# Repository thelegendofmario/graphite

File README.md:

# Graphite: Custom Graphing calculator

## What is this?

This is a custom-made graphing calculator built off of the [Rasberry Pi Picos](https://www.raspberrypi.com/products/raspberry-pi-pico/).
There are a couple of reasons I chose this board: 
1. they're cheap, and easy to get a hold of.
2. if a new one (with the same form factor and compatible pinout) comes out, you can swap it out, giving you a more powerful cpu, more storage, etc.

## But _Why_ did you make this?

I made this because this is my first ever PCB and thing like this. _Also_, I really wanted to fix some things that I found wrong with the TI-84s and such.

## Bill of Materials:

PCB components: 
| Name | Buy Website | Price | Notes |
| --- | --- | --- | --- |
| 2.2" TFT LCD | https://www.adafruit.com/product/1480 | $24.95 | Just have to use a generic 10 pin thingy 🤷 |
| Rasberry Pi Pico | https://www.adafruit.com/product/4864 | $6.00 |  |
| Buttons | https://www.mouser.com/ProductDetail/Omron-Electronics/B3F-1000?qs=lK7M36XCk6JQHckSc1xIsg%3D%3D | $0.25 | (that's for one, gets cheaper the more you buy yay) |
| male headers | https://www.adafruit.com/product/392 | $4.95 |  |
| 10 pin female headers | https://www.sparkfun.com/header-10-pin-female-pth-0-1.html | $0.80 |  |
| 20 pin female headers | https://www.adafruit.com/product/4155 | $2.50 |  |
|  | Total | $39.45 |  |

---

> project images

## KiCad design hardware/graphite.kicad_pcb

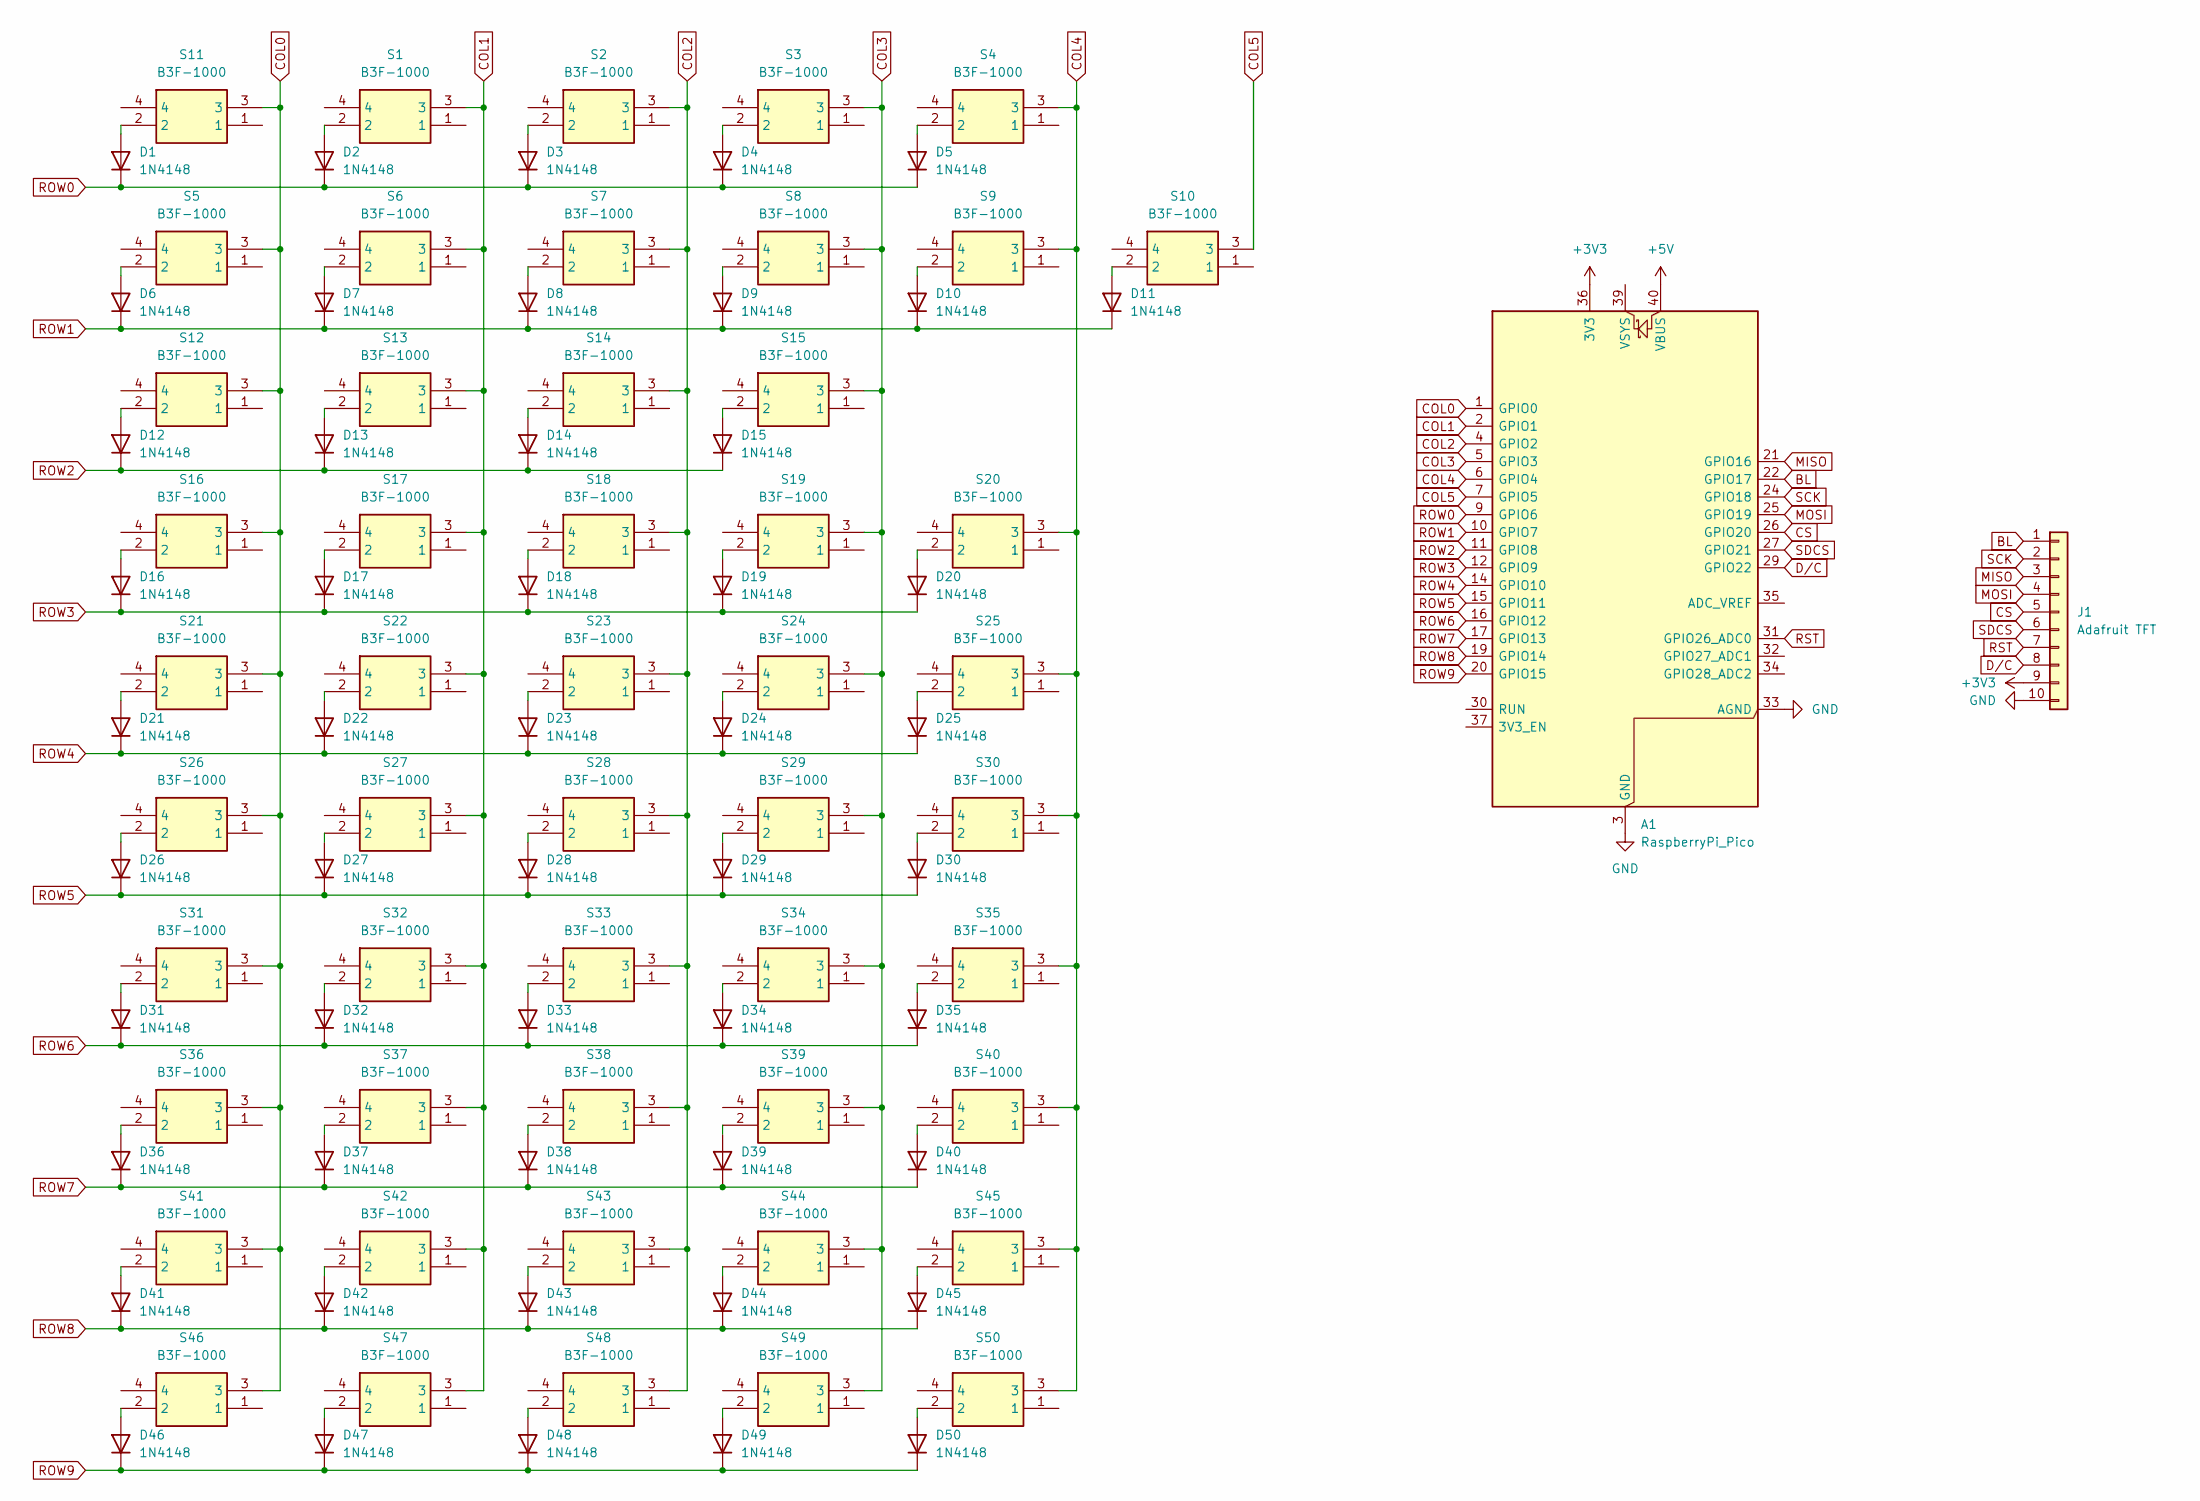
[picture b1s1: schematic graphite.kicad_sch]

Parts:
A1: RaspberryPi_Pico; RaspberryPi_Pico_Common_THT
D1, D2, D3, D4, D5, D6, D7, D8, D9, D10, D11, D12, D13, D14, D15, D16, D17, D18, D19, D20, D21, D22, D23, D24, D25, D26, D27, D28, D29, D30, D31, D32, D33, D34, D35, D36, D37, D38, D39, D40, D41, D42, D43, D44, D45, D46, D47, D48, D49, D50: 1N4148; D_DO-35_SOD27_P7.62mm_Horizontal
J1: Adafruit TFT; PinHeader_1x10_P2.54mm_Vertical
S1, S2, S3, S4, S5, S6, S7, S8, S9, S10, S11, S12, S13, S14, S15, S16, S17, S18, S19, S20, S21, S22, S23, S24, S25, S26, S27, S28, S29, S30, S31, S32, S33, S34, S35, S36, S37, S38, S39, S40, S41, S42, S43, S44, S45, S46, S47, S48, S49, S50: B3F-1000; B3F1002; Mouser Part Number 653-B3F-1000

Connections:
+3V3: A1.36 (3V3), J1.9
+5V: A1.40 (VBUS)
BL: A1.22 (GPIO17), J1.1
COL0: A1.1 (GPIO0), S5.3, S11.3, S12.3, S16.3, S21.3, S26.3, S31.3, S36.3, S41.3, S46.3
COL1: A1.2 (GPIO1), S1.3, S6.3, S13.3, S17.3, S22.3, S27.3, S32.3, S37.3, S42.3, S47.3
COL2: A1.4 (GPIO2), S2.3, S7.3, S14.3, S18.3, S23.3, S28.3, S33.3, S38.3, S43.3, S48.3
COL3: A1.5 (GPIO3), S3.3, S8.3, S15.3, S19.3, S24.3, S29.3, S34.3, S39.3, S44.3, S49.3
COL4: A1.6 (GPIO4), S4.3, S9.3, S20.3, S25.3, S30.3, S35.3, S40.3, S45.3, S50.3
COL5: A1.7 (GPIO5), S10.3
CS: A1.26 (GPIO20), J1.5
D/C: A1.29 (GPIO22), J1.8
GND: A1.3 (GND), A1.8 (GND), A1.13 (GND), A1.18 (GND), A1.23 (GND), A1.28 (GND), A1.33 (AGND), A1.38 (GND), J1.10
MISO: A1.21 (GPIO16), J1.3
MOSI: A1.25 (GPIO19), J1.4
unnamed: D1.2 (A), S11.2
unnamed: D2.2 (A), S1.2
unnamed: D3.2 (A), S2.2
unnamed: D4.2 (A), S3.2
unnamed: D5.2 (A), S4.2
unnamed: D6.2 (A), S5.2
unnamed: D7.2 (A), S6.2
unnamed: D8.2 (A), S7.2
unnamed: D9.2 (A), S8.2
unnamed: D10.2 (A), S9.2
unnamed: D11.2 (A), S10.2
unnamed: D12.2 (A), S12.2
unnamed: D13.2 (A), S13.2
unnamed: D14.2 (A), S14.2
unnamed: D15.2 (A), S15.2
unnamed: D16.2 (A), S16.2
unnamed: D17.2 (A), S17.2
unnamed: D18.2 (A), S18.2
unnamed: D19.2 (A), S19.2
unnamed: D20.2 (A), S20.2
unnamed: D21.2 (A), S21.2
unnamed: D22.2 (A), S22.2
unnamed: D23.2 (A), S23.2
unnamed: D24.2 (A), S24.2
unnamed: D25.2 (A), S25.2
unnamed: D26.2 (A), S26.2
unnamed: D27.2 (A), S27.2
unnamed: D28.2 (A), S28.2
unnamed: D29.2 (A), S29.2
unnamed: D30.2 (A), S30.2
unnamed: D31.2 (A), S31.2
unnamed: D32.2 (A), S32.2
unnamed: D33.2 (A), S33.2
unnamed: D34.2 (A), S34.2
unnamed: D35.2 (A), S35.2
unnamed: D36.2 (A), S36.2
unnamed: D37.2 (A), S37.2
unnamed: D38.2 (A), S38.2
unnamed: D39.2 (A), S39.2
unnamed: D40.2 (A), S40.2
unnamed: D41.2 (A), S41.2
unnamed: D42.2 (A), S42.2
unnamed: D43.2 (A), S43.2
unnamed: D44.2 (A), S44.2
unnamed: D45.2 (A), S45.2
unnamed: D46.2 (A), S46.2
unnamed: D47.2 (A), S47.2
unnamed: D48.2 (A), S48.2
unnamed: D49.2 (A), S49.2
unnamed: D50.2 (A), S50.2
ROW0: A1.9 (GPIO6), D1.1 (K), D2.1 (K), D3.1 (K), D4.1 (K), D5.1 (K)
ROW1: A1.10 (GPIO7), D6.1 (K), D7.1 (K), D8.1 (K), D9.1 (K), D10.1 (K), D11.1 (K)
ROW2: A1.11 (GPIO8), D12.1 (K), D13.1 (K), D14.1 (K), D15.1 (K)
ROW3: A1.12 (GPIO9), D16.1 (K), D17.1 (K), D18.1 (K), D19.1 (K), D20.1 (K)
ROW4: A1.14 (GPIO10), D21.1 (K), D22.1 (K), D23.1 (K), D24.1 (K), D25.1 (K)
ROW5: A1.15 (GPIO11), D26.1 (K), D27.1 (K), D28.1 (K), D29.1 (K), D30.1 (K)
ROW6: A1.16 (GPIO12), D31.1 (K), D32.1 (K), D33.1 (K), D34.1 (K), D35.1 (K)
ROW7: A1.17 (GPIO13), D36.1 (K), D37.1 (K), D38.1 (K), D39.1 (K), D40.1 (K)
ROW8: A1.19 (GPIO14), D41.1 (K), D42.1 (K), D43.1 (K), D44.1 (K), D45.1 (K)
ROW9: A1.20 (GPIO15), D46.1 (K), D47.1 (K), D48.1 (K), D49.1 (K), D50.1 (K)
RST: A1.31 (GPIO26_ADC0), J1.7
SCK: A1.24 (GPIO18), J1.2
SDCS: A1.27 (GPIO21), J1.6

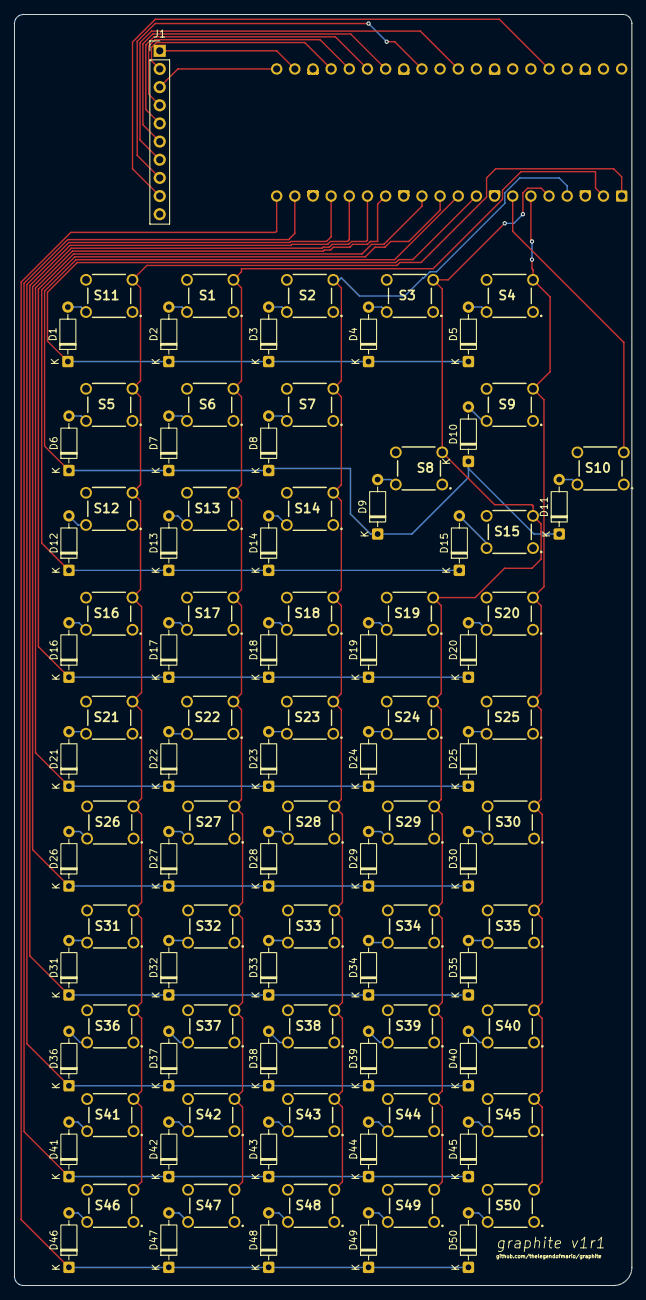
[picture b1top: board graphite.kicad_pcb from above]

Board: 2 copper layers, 86.4 x 177.8 mm, 102 parts (1 on the bottom side), 76 nets.

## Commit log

2025-05-24 Rename Screenshot From 2025-05-24 15-14-00.png to bom.png
2025-06-02 made it slightly more organized
2025-06-02 chore: hopefully actually wired screen correctly lol
2025-06-03 feat: finished schematic
2025-06-09 chore: tidied up schematic
2025-06-09 feat: FINALLY working on pcb
2025-06-09 feat: finished routing :tada:
2025-06-10 chore: polished pcb
2025-06-11 Update BOM.csv with even _more_ headers
2025-06-16 Update README.md, ready for subbmission :happy:
2025-06-16 oh crap frogot bom
2025-06-16 polished pcb, tbh i don't even remember what else I did on this commit lol also forgot to commit
2025-06-16 polish bom in readme
2025-06-16 add case source files
2025-06-27 added better 3d models
2025-06-27 updated case source
2025-06-30 upload full model of case
